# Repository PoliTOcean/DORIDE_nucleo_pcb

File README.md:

# NOME_REPO

> **Hai appena creato la repo da questo template? Fai questi passi, poi cancella questo riquadro.**
>
> 1. Rinomina la repo nel formato `<rov>_<componente>_pcb` (es. `nereo_power_pcb`).
> 2. Aggiungi il topic **`electronics`** (ingranaggio accanto ad "About"). I topic non vengono copiati dal template.
> 3. *Settings → Pages → Deploy from a branch → main → /docs → Save*.
> 4. Metti il progetto KiCad dentro `hardware/` (un solo `.kicad_pro`), con le librerie della scheda in `hardware/lib/local/`.
> 5. Sostituisci `NOME_REPO`, `NOME_PROGETTO` e il link al firmware qui sotto. `NOME_PROGETTO` è il nome del file `.kicad_pro` senza estensione.
> 6. Fai `git pull` prima di ogni modifica: dopo ogni push il bot aggiunge i render.

Descrizione della scheda (ROV, funzione, microcontrollore, numero di layer).
Firmware: [NOME_REPO_FIRMWARE](https://github.com/PoliTOcean/NOME_REPO_FIRMWARE)

| Top | Bottom |
|---|---|
|  |  |

## File di produzione

Gerber, forature e PDF dello schema si scaricano da **Actions → ultima run → pcb-outputs**.

## Struttura

~~~
hardware/            progetto KiCad
hardware/lib/local/  simboli, footprint e modelli 3D usati solo da questa scheda
docs/                render e interactive BOM (generati dal bot, non modificare)
~~~

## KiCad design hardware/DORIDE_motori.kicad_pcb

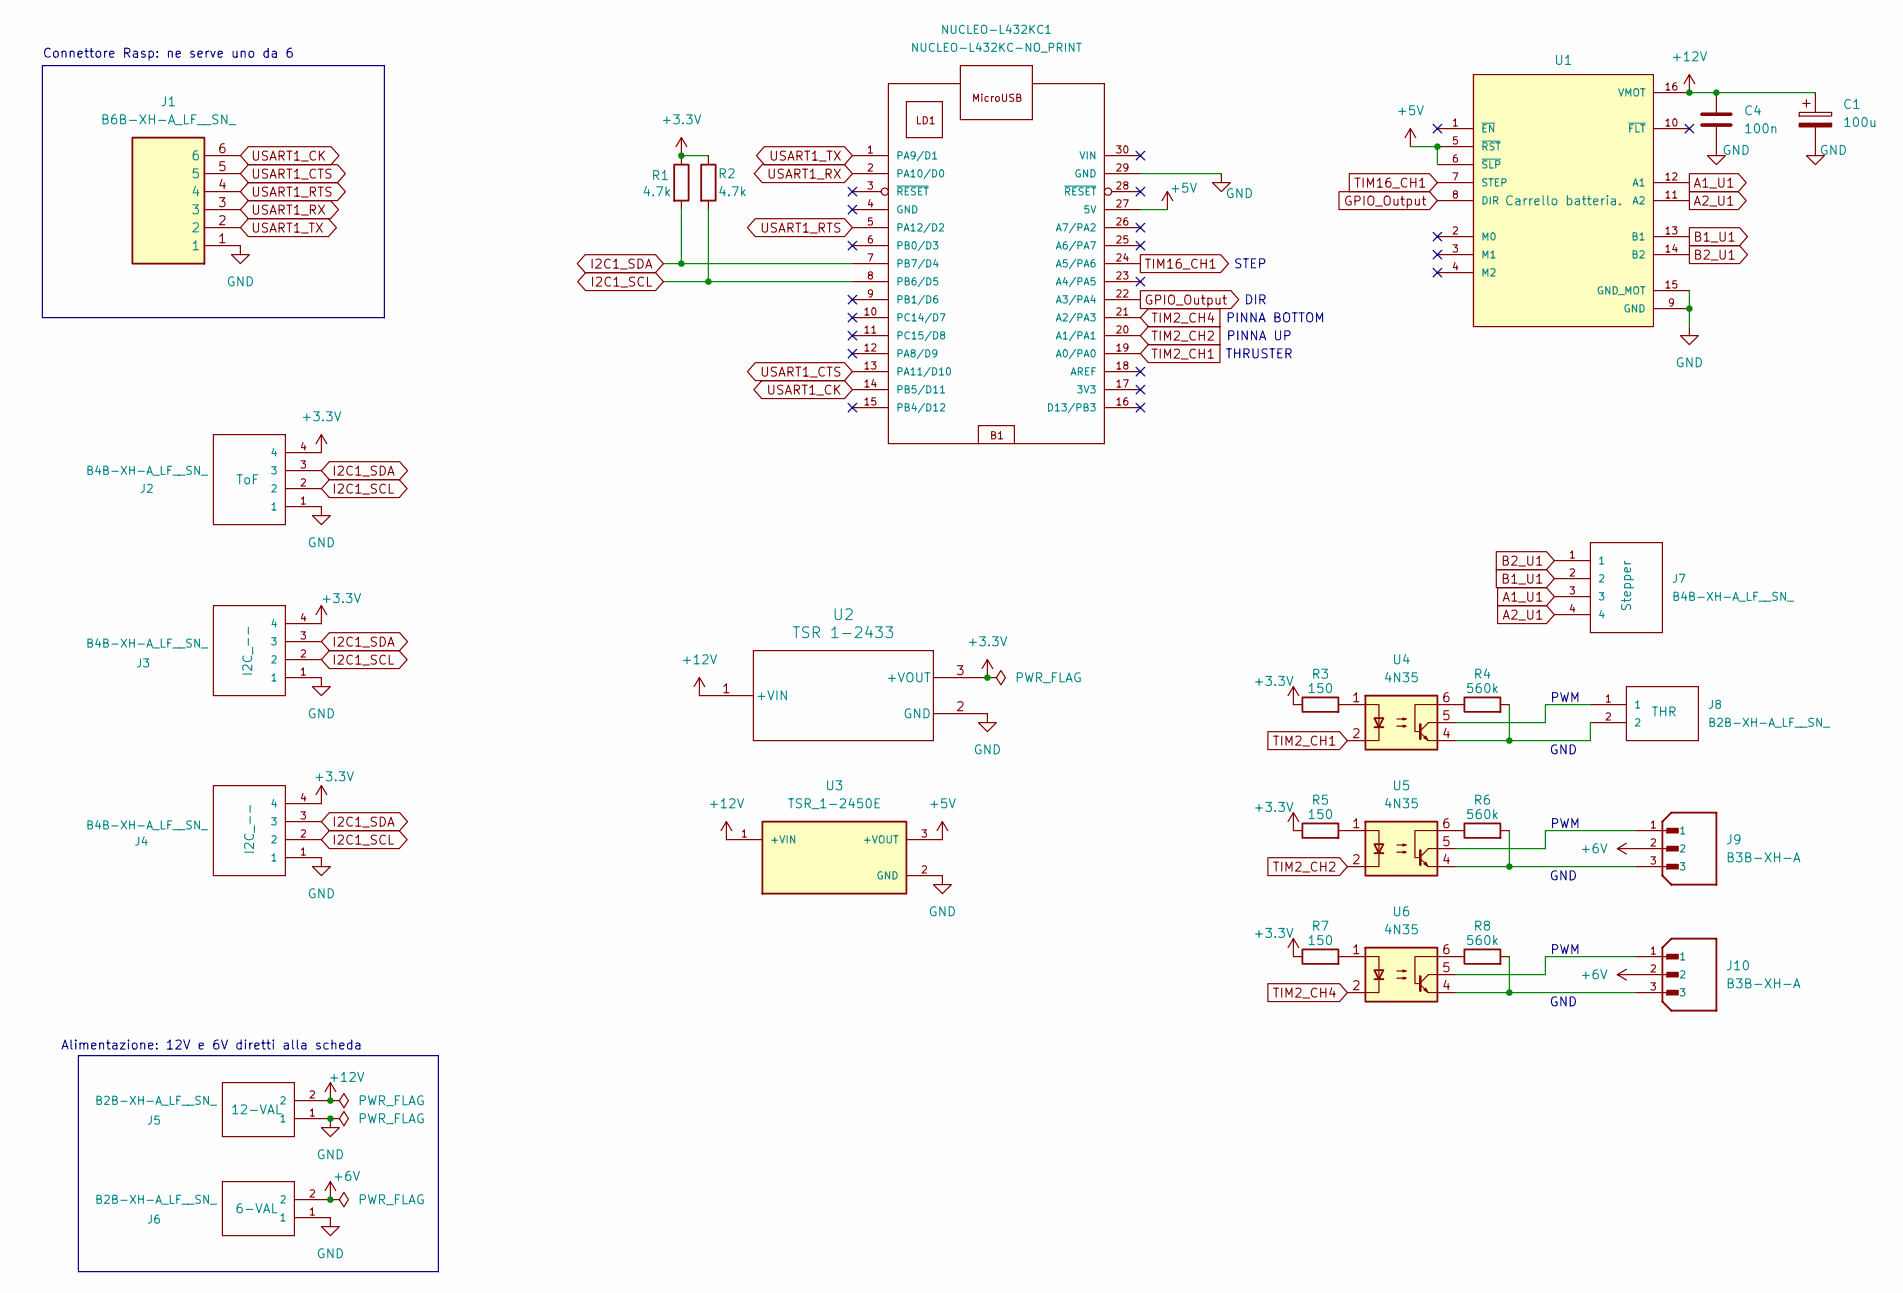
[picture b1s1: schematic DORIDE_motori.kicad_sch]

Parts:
C1: 100u; CP_Elec_6.3x7.7
C4: 100n; C_0603_1608Metric
J1: B6B-XH-A_LF__SN_; SHDR6W64P0X250_1X6_1740X575X700P; Mouser Part Number 306-B6BXHALFSN
J2, J3, J4, J7: B4B-XH-A_LF__SN_; SHDR4W64P0X250_1X4_1240X575X70
J5, J6, J8: B2B-XH-A_LF__SN_; SHDR2W64P0X250_1X2_740X575X700
J9, J10: B3B-XH-A; SHDR3W64P0X250_1X3_990X575X700; PARTREV 7/4/21
NUCLEO-L432KC1: NUCLEO-L432KC-NO_PRINT; NUCLEO-L432KC
R1, R2: 4.7k; R_0603_1608Metric
R3, R5, R7: 150; R_0603_1608Metric
R4, R6, R8: 560k; R_0603_1608Metric
U1: DRV8825_STEPPER_MOTOR_DRIVER_SMALL_BOARD; IC_DRV8825_STEPPER_MOTOR_DRIVER_CARRIER
U2: TSR 1-2433; TSR1-2433
U3: TSR_1-2450E; CONV_TSR_1-2450E; PARTREV May 25, 2020
U4, U5, U6: 4N35; DIP-6_W7.62mm

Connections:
+3.3V: J2.4, J3.4, J4.4, R1.1, R2.1, R3.1, R5.1, R7.1, U2.3 (+VOUT)
+5V: NUCLEO-L432KC1.27 (5V), U1.5 (~RST), U1.6 (~SLP), U3.3 (+VOUT)
+6V: J6.2, J9.2, J10.2
+12V: C1.1, C4.1, J5.2, U1.16 (VMOT), U2.1 (+VIN), U3.1 (+VIN)
A1_U1: J7.3, U1.12 (A1)
A2_U1: J7.4, U1.11 (A2)
B1_U1: J7.2, U1.13 (B1)
B2_U1: J7.1, U1.14 (B2)
GND: C1.2, C4.2, J1.1, J2.1, J3.1, J4.1, J5.1, J6.1, NUCLEO-L432KC1.29 (GND), U1.9 (GND), U1.15 (GND_MOT), U2.2 (GND), U3.2 (GND)
GPIO_Output: NUCLEO-L432KC1.22 (A3/PA4), U1.8 (DIR)
I2C1_SCL: J2.2, J3.2, J4.2, NUCLEO-L432KC1.8 (PB6/D5), R2.2
I2C1_SDA: J2.3, J3.3, J4.3, NUCLEO-L432KC1.7 (PB7/D4), R1.2
unnamed: J8.1, U4.5
unnamed: J8.2, R4.2, U4.4
unnamed: J9.1, U5.5
unnamed: J9.3, R6.2, U5.4
unnamed: J10.1, U6.5
unnamed: J10.3, R8.2, U6.4
unnamed: R3.2, U4.1
unnamed: R4.1, U4.6
unnamed: R5.2, U5.1
unnamed: R6.1, U5.6
unnamed: R7.2, U6.1
unnamed: R8.1, U6.6
TIM2_CH1: NUCLEO-L432KC1.19 (A0/PA0), U4.2
TIM2_CH2: NUCLEO-L432KC1.20 (A1/PA1), U5.2
TIM2_CH4: NUCLEO-L432KC1.21 (A2/PA3), U6.2
TIM16_CH1: NUCLEO-L432KC1.24 (A5/PA6), U1.7 (STEP)
USART1_CK: J1.6, NUCLEO-L432KC1.14 (PB5/D11)
USART1_CTS: J1.5, NUCLEO-L432KC1.13 (PA11/D10)
USART1_RTS: J1.4, NUCLEO-L432KC1.5 (PA12/D2)
USART1_RX: J1.3, NUCLEO-L432KC1.2 (PA10/D0)
USART1_TX: J1.2, NUCLEO-L432KC1.1 (PA9/D1)

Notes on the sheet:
Connettore Rasp: ne serve uno da 6
DIR
GND
PWM
STEP
Alimentazione: 12V e 6V diretti alla scheda
THRUSTER
PINNA BOTTOM
PINNA UP

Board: 2 copper layers, 27 parts (0 on the bottom side), 33 nets, no tracks yet.
